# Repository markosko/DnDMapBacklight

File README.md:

View this project on [CADLAB.io](https://cadlab.io/project/30086). 

# DnDMapBacklight

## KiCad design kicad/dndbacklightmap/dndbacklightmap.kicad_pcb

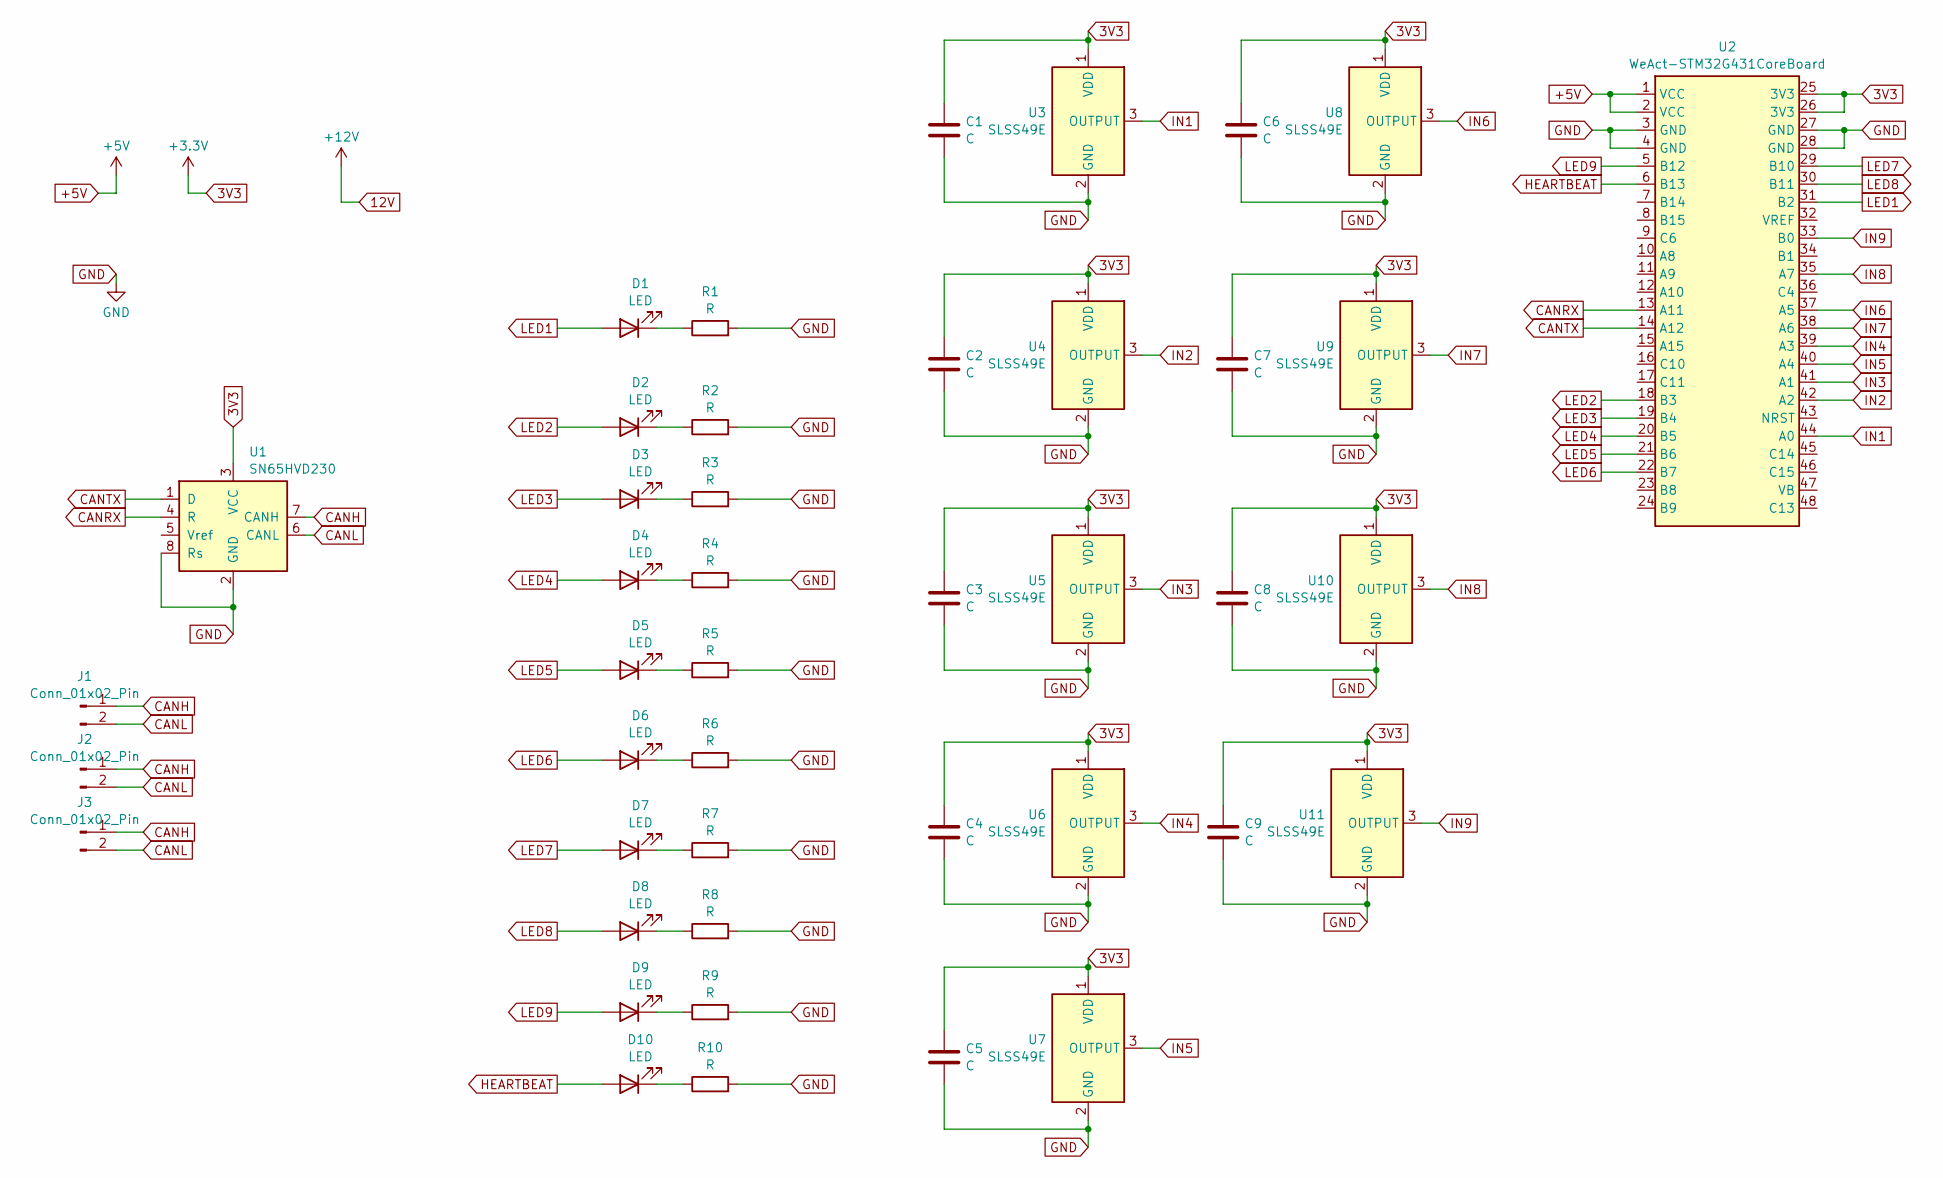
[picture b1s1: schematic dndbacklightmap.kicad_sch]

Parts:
C1, C2, C3, C4, C5, C6, C7, C8, C9: C; C_1206_3216Metric_Pad1.33x1.80mm_HandSolder
D1, D2, D3, D4, D5, D6, D7, D8, D9, D10: LED; LED_1206_3216Metric_Pad1.42x1.75mm_HandSolder
J1, J2, J3: Conn_01x02_Pin
R1, R2, R3, R4, R5, R6, R7, R8, R9, R10: R; R_1206_3216Metric_Pad1.30x1.75mm_HandSolder
U1: SN65HVD230; SOIC-8_3.9x4.9mm_P1.27mm
U2: WeAct-STM32G431CoreBoard; WeAct-STM32G431CoreBoard_MCU_SMT
U3, U4, U5, U6, U7, U8, U9, U10, U11: SLSS49E; SOT-23

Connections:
3V3: C1.1, C2.1, C3.1, C4.1, C5.1, C6.1, C7.1, C8.1, C9.1, U1.3 (VCC), U2.25 (3V3), U2.26 (3V3), U3.1 (VDD), U4.1 (VDD), U5.1 (VDD), U6.1 (VDD), U7.1 (VDD), U8.1 (VDD), U9.1 (VDD), U10.1 (VDD), U11.1 (VDD)
+5V: U2.1 (VCC), U2.2 (VCC)
CANH: J1.1, J2.1, J3.1, U1.7 (CANH)
CANL: J1.2, J2.2, J3.2, U1.6 (CANL)
CANRX: U1.4 (R), U2.13 (A11)
CANTX: U1.1 (D), U2.14 (A12)
GND: C1.2, C2.2, C3.2, C4.2, C5.2, C6.2, C7.2, C8.2, C9.2, R1.2, R2.2, R3.2, R4.2, R5.2, R6.2, R7.2, R8.2, R9.2, R10.2, U1.2 (GND), U1.8 (Rs), U2.3 (GND), U2.4 (GND), U2.27 (GND), U2.28 (GND), U3.2 (GND), U4.2 (GND), U5.2 (GND), U6.2 (GND), U7.2 (GND), U8.2 (GND), U9.2 (GND), U10.2 (GND), U11.2 (GND)
HEARTBEAT: D10.2 (A), U2.6 (B13)
IN1: U2.44 (A0), U3.3 (OUTPUT)
IN2: U2.42 (A2), U4.3 (OUTPUT)
IN3: U2.41 (A1), U5.3 (OUTPUT)
IN4: U2.39 (A3), U6.3 (OUTPUT)
IN5: U2.40 (A4), U7.3 (OUTPUT)
IN6: U2.37 (A5), U8.3 (OUTPUT)
IN7: U2.38 (A6), U9.3 (OUTPUT)
IN8: U2.35 (A7), U10.3 (OUTPUT)
IN9: U2.33 (B0), U11.3 (OUTPUT)
LED1: D1.2 (A), U2.31 (B2)
LED2: D2.2 (A), U2.18 (B3)
LED3: D3.2 (A), U2.19 (B4)
LED4: D4.2 (A), U2.20 (B5)
LED5: D5.2 (A), U2.21 (B6)
LED6: D6.2 (A), U2.22 (B7)
LED7: D7.2 (A), U2.29 (B10)
LED8: D8.2 (A), U2.30 (B11)
LED9: D9.2 (A), U2.5 (B12)
unnamed: D1.1 (K), R1.1
unnamed: D2.1 (K), R2.1
unnamed: D3.1 (K), R3.1
unnamed: D4.1 (K), R4.1
unnamed: D5.1 (K), R5.1
unnamed: D6.1 (K), R6.1
unnamed: D7.1 (K), R7.1
unnamed: D8.1 (K), R8.1
unnamed: D9.1 (K), R9.1
unnamed: D10.1 (K), R10.1

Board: 2 copper layers, 40 parts (4 on the bottom side), 34 nets, no tracks yet.

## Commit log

2026-02-17 remove files
2026-02-17 Backlink to CADLAB.io has been added.
2026-02-17 step file
2026-02-17 stl file
2026-02-17 rotation of components
